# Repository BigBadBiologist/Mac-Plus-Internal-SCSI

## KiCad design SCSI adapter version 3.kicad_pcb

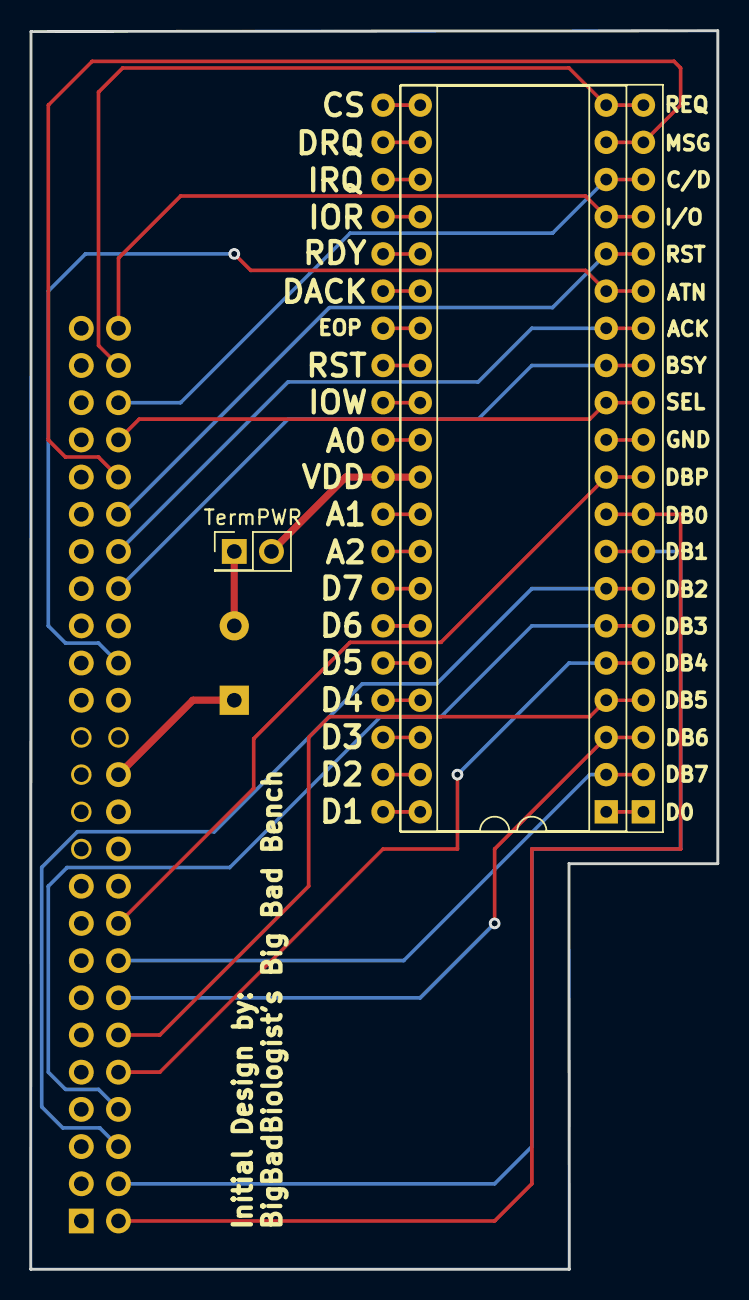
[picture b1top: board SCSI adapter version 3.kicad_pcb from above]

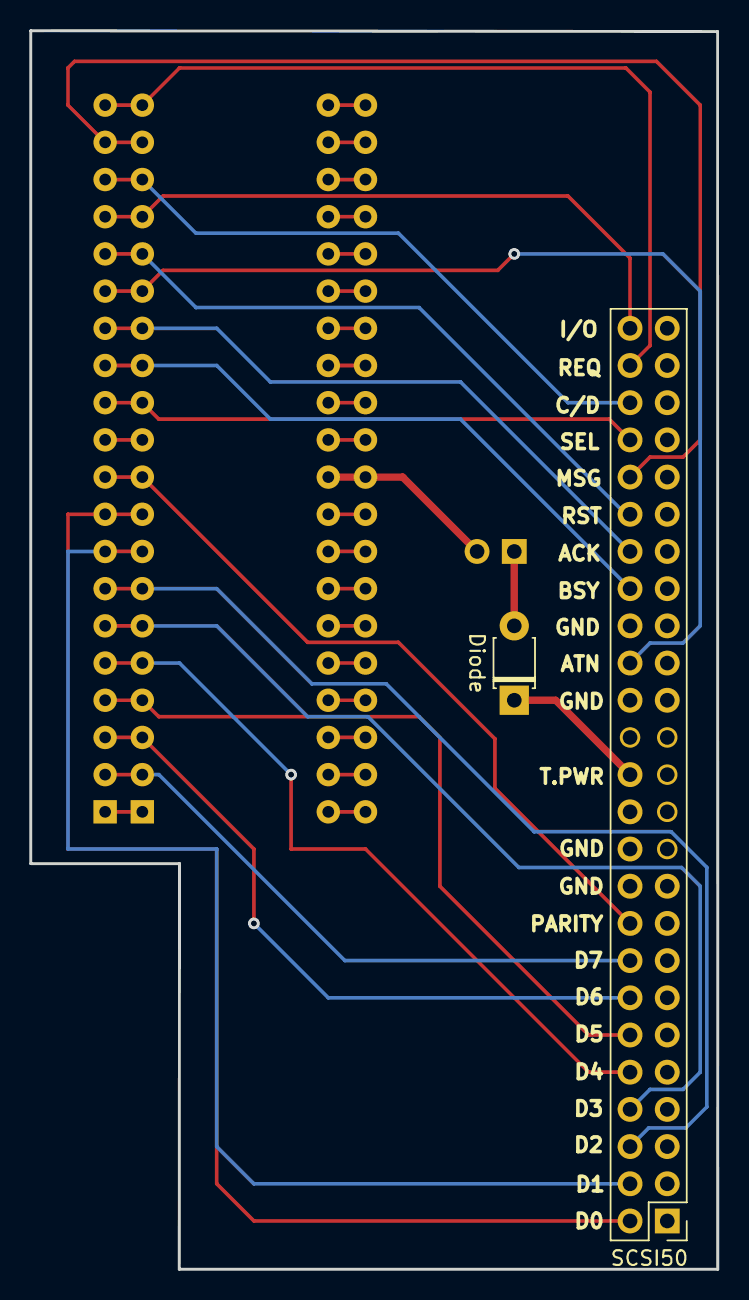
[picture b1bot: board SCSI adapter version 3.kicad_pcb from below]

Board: 4 copper layers, 46.9 x 84.6 mm, 5 parts (2 on the bottom side), 20 nets.

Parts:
<-Socket: DIP-40_W15.24mm_Socket
<-Socket#2: DIP-40_W15.24mm
Diode: D_T-1_P5.08mm_Horizontal
SCSI50: PinHeader_2x25_P2.54mm_Vertical
TermPWR: PinHeader_2x01_P2.54mm_Vertical

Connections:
ACK: <-Socket.14, <-Socket#2.14, SCSI50.38
ATN: <-Socket.15, <-Socket#2.15, SCSI50.32
BSY: <-Socket.13, <-Socket#2.13, SCSI50.36
C/D: <-Socket.18, <-Socket#2.18, SCSI50.46
D0: <-Socket.9, <-Socket#2.9, SCSI50.2
D1: <-Socket.8, <-Socket#2.8, SCSI50.4
D2: <-Socket.7, <-Socket#2.7, SCSI50.6
D3: <-Socket.6, <-Socket#2.6, SCSI50.8
D4: <-Socket.5, <-Socket#2.5, SCSI50.10
D5: <-Socket.4, <-Socket#2.4, SCSI50.12
D6: <-Socket.3, <-Socket#2.3, SCSI50.14
D7: <-Socket.2, <-Socket#2.2, SCSI50.16
GND: <-Socket.11, <-Socket#2.11, SCSI50.1, SCSI50.3, SCSI50.5, SCSI50.7, SCSI50.9, SCSI50.11, SCSI50.13, SCSI50.15, SCSI50.17, SCSI50.19, SCSI50.20, SCSI50.22, SCSI50.29, SCSI50.30, SCSI50.31, SCSI50.33, SCSI50.34, SCSI50.35, SCSI50.37, SCSI50.39, SCSI50.41, SCSI50.43, SCSI50.45, SCSI50.47, SCSI50.49
I/O: <-Socket.17, <-Socket#2.17, SCSI50.50
MSG: <-Socket.19, <-Socket#2.19, SCSI50.42
REQ: <-Socket.20, <-Socket#2.20, SCSI50.48
RST: <-Socket.16, <-Socket#2.16, SCSI50.40
SEL: <-Socket.12, <-Socket#2.12, SCSI50.44
VDD/Tpower: <-Socket.31, <-Socket#2.31, Diode.1, Diode.2, SCSI50.26, TermPWR.1, TermPWR.2
parity: <-Socket.10, <-Socket#2.10, SCSI50.18

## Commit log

2023-05-20 PCB files uploaded
    Gerber and Kicad files uploaded
2023-05-29 Updated files and added readme
    The previous collection was missing a couple files. I also added a zip file of all the required files for PCB creation.
2023-05-30 Updated the files with the latest version of KiCad
    My KiCad was out of date, so I updated it and then re-exported all the files.
2023-06-04 Update ReadMe.rtf
    Added link to install video
